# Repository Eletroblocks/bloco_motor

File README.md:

# motor
Utiliza a energia elétrica recebida para produzir MOVIMENTO CONTÍNUO.

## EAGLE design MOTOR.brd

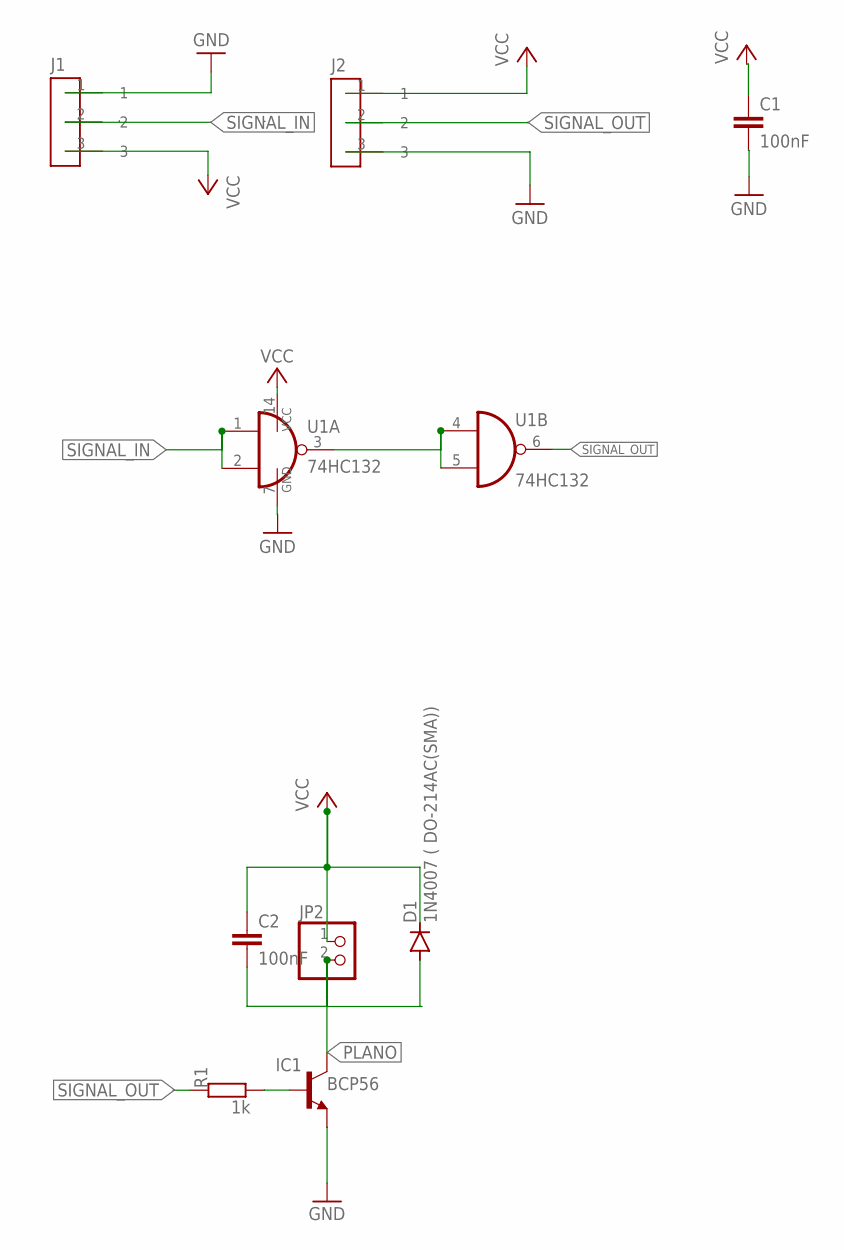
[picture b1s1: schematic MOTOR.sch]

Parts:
C1, C2: 100nF; C0805
D1: 1N4007 ( DO-214AC(SMA)); SMA-DO214AC
IC1: BCP56; SOT223
J1: CONECTOR_MACHO; MALE
J2: CONECTOR_FEMEA; FEMALE
JP2: PINHD-1X2; 1X02
R1: 1k; R0805W
U1: 74HC132; SO14

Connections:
GND: C1.2, IC1.3 (E), J1.1, J2.3, U1.7 (GND)
unnamed: IC1.1 (B), R1.1
unnamed: U1.3 (O), U1.4 (I0), U1.5 (I1)
PLANO: C2.2, D1.A, IC1.4 (C), JP2.2
SIGNAL_IN: J1.2, U1.1 (I0), U1.2 (I1)
SIGNAL_OUT: J2.2, R1.2, U1.6 (O)
VCC: C1.1, C2.1, D1.K (C), J1.3, J2.1, JP2.1, U1.14 (VCC)

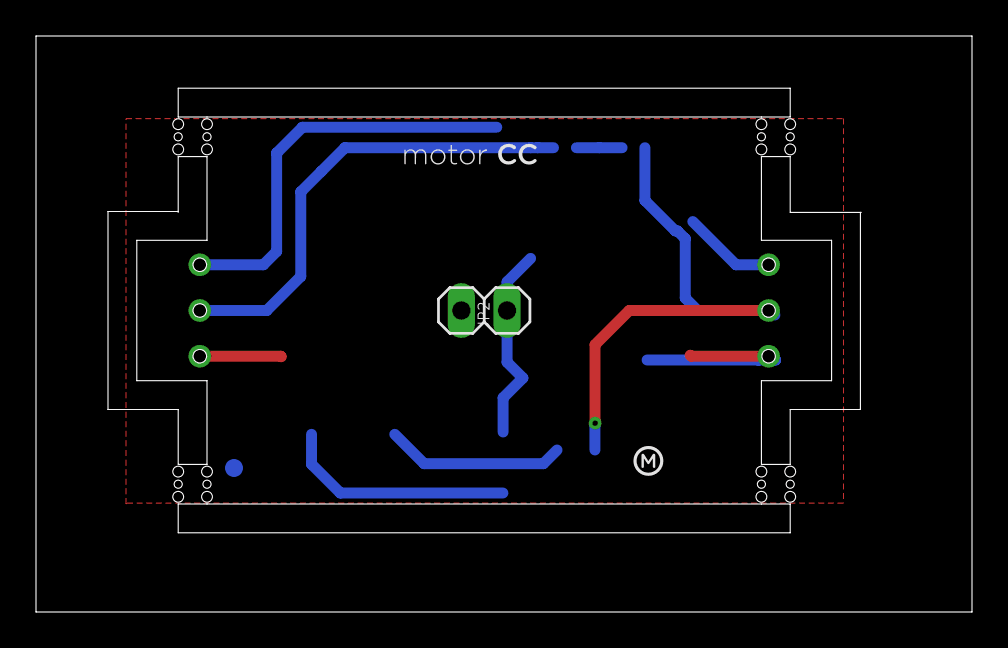
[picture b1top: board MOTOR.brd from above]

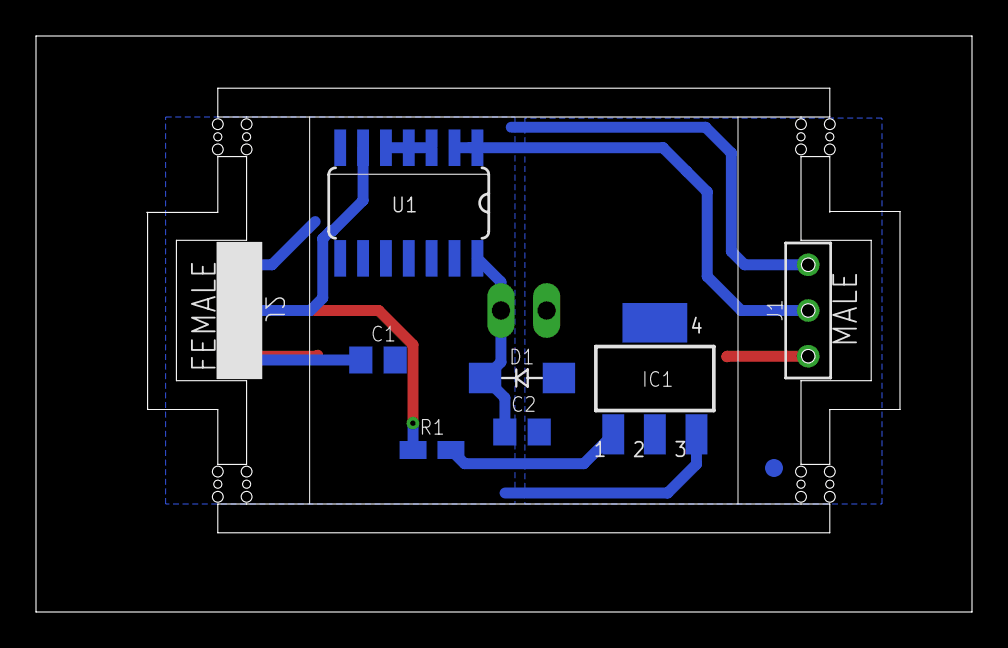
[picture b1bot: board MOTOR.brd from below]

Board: 2 copper layers, 52.0 x 32.0 mm, 14 parts (7 on the bottom side), 7 nets.

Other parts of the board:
U$1: FIDUCIAL_G10
U$2, U$3, U$4, U$5: STAMP_DUPLO

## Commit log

2020-11-23 init project
2020-11-23 correção de pads, adição de label para versionamento e plano de VCC
2020-11-23 correção de label
2020-12-28 organizando arquivos
2020-12-28 imagem
2021-03-11 V1.0.2

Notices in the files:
parts and their libraries:
dicons: Copyright (C) 2004, Bob Starr (rtzaudio@mindspring.com)
